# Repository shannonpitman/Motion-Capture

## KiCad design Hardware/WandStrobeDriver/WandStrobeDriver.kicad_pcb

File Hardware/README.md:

# Hardware — strobed wand for extrinsic calibration

KiCad 10 schematics for the pulsed marker wand that feeds `OpenMV/ExtrinsicsCalib`.
Two boards, schematic-only so far (no PCB layout yet).

| Directory | Build | Parts | Does |
|---|---|---|---|
| `WandStrobeDriver/` | ×1, at the handle | 20 | TLC555 astable + high-side P-FET; strobes all four markers together |
| `WandMarker/` | ×4, one per marker | 8 | 4× Kingbright L-7113SF7C in series + one ballast resistor |

```bash
python3 gen_schematics.py
```

`gen_schematics.py` writes both `.kicad_sch` files; change a value there and re-run
rather than editing the schematic by hand. `kisch.py` is a minimal schematic writer
and `kisym.py` pulls symbol geometry out of the stock KiCad libraries, so wire
endpoints come from real pin positions instead of being typed in.

## Rev B — what changed and why

Rev A ran **12 V** and put a **constant-current sink** on every marker board.
Both are gone.

The sink cost 1.6 V of headroom — a Vbe of sense, a Vce of regulation, and the
input Schottky — and that 1.6 V was the *entire* reason rev A needed 12 V. What it
bought was marker-to-marker matching of roughly 5 %. The bench data already shows
σ moving only ~3 % across a 20 % exposure range, and run-to-run repeatability of
the characterisation itself is ~3 %. So the sink was buying matching finer than the
measurement can resolve, at the price of a higher supply and eight extra parts per
marker board.

**The marker board is now the board that was already characterised, plus a
connector.** That is also why the existing boards plug straight into the driver.

Rev A is in git history if supply sensitivity ever turns out to matter.

## The rig

```
D
|
|                 D arm perpendicular at A, length >= |AC|/3
A-------------B---------C
<-----2/3-----><--1/3--->
```

A = origin, C = +X, D = +Y, as `ExtrinsicsCalib/README.md` defines them. Two wires
run from the driver to each marker: switched +9 V and a common ground. One timer
drives all four, so "dark" always means occluded, never out of phase.

## Why there is no diode across R2

This is the one place where the obvious simplification is the wrong one.

The standard trick for sub-50 % duty on a 555 is a diode across R2, and it assumes
the LEDs are on when **OUT is high**. They are not. `Q1` is P-channel on the
**high side** and conducts when **OUT is low** — so the short state is already the
state we want, and a plain astable with `R1 >> R2` gives 0.36 % duty with no diode
at all.

Adding the diode would force `R1` small, and `R1` then sinks `Vcc/R1` through the
DISCH pin for the whole 327 ms off-time — about **20 mA**, on a battery, against
the **9 µA** the circuit actually draws as built.

High-side switching also means every marker's return is permanently grounded, so a
chafed wire against the frame is a non-event rather than a short.

## Timing — three fixed parts

```
t_on   = 0.693 · R2 · C6              1075 µs
t_off  = 0.693 · (R1+R2) · C6          327 ms      ->  3.05 Hz
```

`R1 = 1 M`, `R2 = 3k3`, `C6 = 470 nF`. 1 MΩ is legal **only** because the TLC555 is
CMOS (pA input current); a bipolar NE555 would not hold this operating point.

3 Hz is `buildEasyWand`'s default `PulseHz`. Pulse grouping needs frame period <
pulse period with margin, and the 555 is a free-running RC oscillator — expect a few
percent of error and drift. That is fine, because alignment fits an offset and rate
per camera. Do not treat the strobe period as a known constant.

**`R2` sets pulse width, which is the brightness control.** Peak current is fixed by
the ballast resistor on each marker board, so the light delivered into one exposure
is `I × t_on`. Fit `R2` through-hole and clip a 5 k pot across its pads for bring-up,
then solder the nearest E24 value. The rate barely moves with it:

| R2 | t_on | | R2 | t_on |
|---|---|---|---|---|
| 1k8 | 586 µs | | **3k3** | **1075 µs** (fitted) |
| 2k2 | 717 µs | | 3k9 | 1270 µs |
| 2k7 | 879 µs | | 4k7 | 1531 µs |

**Every resistor on both boards is an E12 value** — 1M, 3k3, 220, 100k, 22k, 100,
and 68R on the markers. Nothing needs series pairs or an E24 stock.

The exact number does not matter. The 470 nF film capacitor is ±5 % on its own,
which is ±54 µs — larger than the gap between adjacent E12 steps at this end of
the range. `R2` is set empirically against a camera reading anyway, so treat
whatever you fit as a starting point.

## Supply — 9 V is sufficient

| Load | Average |
|---|---|
| TLC555 | ~1 mA |
| Timing network | 9 µA |
| D2 power indicator | ~0.35 mA |
| LEDs, 4 × 36 mA × 0.36 % | 0.52 mA |
| **Total** | **~1.9 mA** |

6×AA alkaline, or a PP3 for bench work. The timer, not the LEDs, dominates.

Headroom at 9 V, after the input Schottky (0.45 V) and bulk-cap droop (~0.2 V),
leaves 8.35 V across four LEDs and the ballast resistor. Comfortable — the string is
about 5.9 V, not the 6.4 V a flat 1.6 V per LED would suggest (see below).

`C1 = 1000 µF` covers the pulse: 4 × 36 mA × 1173 µs = 169 µC → 0.17 V droop.

## The emitter

**Kingbright L-7113SF7C**, 5 mm through-hole, GaAlAs, 850 nm (datasheet DSAB9772 V.16B).

| Parameter | Value | Conditions |
|---|---|---|
| Forward voltage | 1.4 typ / **1.6 max** | **at I_F = 20 mA** |
| DC forward current | **50 mA** | absolute max |
| Peak forward current | 1 A | 1/100 duty, **10 µs** pulse width |
| Power dissipation | 80 mW | absolute max |
| Radiant intensity | 30 typ mW/sr @ 20 mA, 90 @ 50 mA | |
| Viewing angle 2θ½ | **20°** | narrow — this is the ring artefact |

**1.6 V is not "the" forward drop.** It is the maximum *at 20 mA*. Vf climbs with
current and falls below 1.6 V under 20 mA. At 36 mA expect about 1.48 V each, so
four in series is ~5.9 V.

At 36 mA and 0.36 % duty each LED averages **0.19 mW against an 80 mW limit**.

## Setting the LED current

`R1` on each marker board. Same value on all four. Computed at 9 V less the driver's
Schottky and bulk-cap droop, using the real Vf curve rather than a flat 1.6 V:

| R1 | I_LED | Pulse for peak 210 at 4 m | Smear @ 0.3 m/s |
|---|---|---|---|
| 33R | 61 mA | 739 µs | 0.29 px |
| 47R | 48 mA | 951 µs | 0.37 px |
| **68R** | **36 mA** (fitted, matches the bench build) | **1263 µs** | **0.49 px** |
| 100R | 26 mA | 1729 µs | 0.67 px |

Measure across `TP1`–`TP2` with a scope during a pulse: `I = V(TP1) / R1`.

### The price of dropping the constant-current sink

0.3 V of battery sag moves the current **9 %**. The peak pixel value moves with it,
so re-target the exposure occasionally over a long session. It is a slow drift, not
noise, and the bench data shows σ changing only ~3 % across a 20 % exposure range —
so it costs well under 1 % of centroid accuracy. That is the whole trade, stated
plainly.

### Check the workbook number

`LED_characterisation.xlsx` lists **38.2 mA** for this build, computed by
`IR_LED_Parts_Calculator` from an assumed **Vf = 1.6 V** — which is the datasheet
*maximum at 20 mA*, not the value at 38 mA. With the real curve, 9 V through 68 Ω
gives about **43 mA**. Worth measuring once and correcting in the sheet, since that
column appears in the thesis.

## Bench test: build the driver first

Nothing in the driver cares about 9 V versus 12 V — the TLC555 runs 2–15 V and the
P-FET gate swings whatever the rail is. So build the driver, feed it a bench supply,
and hang the **existing** characterisation markers off J2–J5.

| Rail | Existing 68 Ω board draws |
|---|---|
| **9 V** | **36 mA** — the characterised operating point |
| 12 V | 74 mA |

At 9 V the strobe test is directly comparable with the DC rows in `A_Bench`. The
equivalence worth confirming is that the *peak pixel value* matches the DC bench row
once `R2` is set, because the camera in Regime B sees the peak, not the average.

Probe `TP1` (gate) against `TP3` (GND) on a scope before connecting any LED — that
confirms period and pulse width on their own.

## Breadboard variant — N-channel low side

The PCB uses a P-channel high-side switch. If the only MOSFETs to hand are
N-channel (IRF540N, IRF1010E), the bench build changes topology but nothing
optical or timing-related, so it still verifies what the breadboard is for.

**Move the switch to the low side.** All four marker grounds go to the FET
drain; source to GND; gate from the 555 through `R3`. An N-channel conducts
when the gate is **high**, so the flash must now be the OUT-**high** state —
the opposite of the PCB — which means the diode across R2 is now required.

| | PCB (P-ch high side) | Breadboard (N-ch low side) |
|---|---|---|
| `R1` charge path | 1 M | **3k3** |
| `R2` discharge | 3k3 | **1 M** |
| Diode across `R2` | none | **1N4148**, anode at DISCH, cathode at THR/TRIG |
| LEDs lit when OUT is | low | **high** |

Swap the two resistor values and add the diode. Timing comes out the same:
`t_on = 0.693 · 3k3 · 470n = 1075 µs`, `f = 3.06 Hz`, duty 0.33 %.

**What it costs.** During the 326 ms off-time the DISCH pin sinks `Vcc/R1` =
**2.7 mA** continuously, so the board goes from 1.9 mA to 4.6 mA average —
about 540 h on 6×AA instead of 1300. Fine for bench work, which is why the
PCB keeps the P-channel version.

(An earlier note in this file put that penalty at ~20 mA. That figure was for
rev A's 12 V rail and 300 µs pulse, where `R1` would have been ~920 Ω. At rev
B's 9 V and 1075 µs, `R1` is 3k3 and the penalty is 2.7 mA.)

**Headroom is unchanged** — 11 mV across an IRF540N at 144 mA against 10 mV
for the P-channel part. Both are irrelevant.

**What you lose:** with low-side switching the marker returns are no longer
permanently grounded, so the "a chafed wire against the frame is a non-event"
property goes away. Irrelevant on an isolated breadboard; it is one of the
reasons the PCB stays high-side.

Either FET works. Prefer the **IRF540N** — 71 nC of gate charge against the
IRF1010E's ~130 nC, and it only needs ~4 V of gate to pass 144 mA, so the
TLC555 drives it directly through `R3` with a few microseconds of edge against
a 1075 µs pulse. V_GS(th) is 2.0–4.0 V and V_GS max is ±20 V, so a 9 V swing
turns it hard on and stays well inside the gate rating.

**TO-220 tab is the DRAIN on both parts.** Low side, that puts the tab on the
marker-return node, not ground — keep it clear of anything earthed.

## Two parts you must not substitute casually

**Q1 (driver).** `DMP3098L-7` — **P-channel enhancement mode**, SOT-23
(Diodes Inc DS31447). The ratings that matter here:

| Parameter | Value | Why it matters |
|---|---|---|
| V_GSS | **±20 V** | the gate swings the whole rail, so this must exceed 9 V |
| V_GS(th) | −1.0 / −1.8 / −2.1 V | at −9 V the part is hard on, far past threshold |
| R_DS(on) | 70 mΩ max @ V_GS = −10 V | 10 mV across it at the 144 mA pulse |
| V_DSS | −30 V | 3× the rail |
| I_D | −3.8 A cont., −11 A pulsed | wildly over-specified at 144 mA, which is fine |
| Q_g | 7.8 nC @ −10 V | ~190 ns edge through R3, against a 1173 µs pulse |

**It must be enhancement mode, not depletion.** An enhancement device is OFF at
V_GS = 0, which is what R4 holds it at whenever the timer is not driving — so a
missing or unpowered TLC555 leaves the markers dark. A depletion device is ON at
V_GS = 0 and would sit the strings at DC with no strobe at all.

Any substitute needs V_GSS comfortably above 9 V. Do not fit a ±8 V part such as
Si2301; check the rating rather than assuming, since many SOT-23 P-FETs are ±12 V
and some are ±8 V.

**D1–D4 (marker).** Kingbright `L-7113SF7C`, footprint `LED_THT:LED_D5.0mm`. They are
marked **DNP** so a turnkey assembler skips them — they are hand-soldered so the
standoff to the diffuser can be set by hand. DNP excludes a part from the BOM and
position files, **not from the PCB**: the pads are still required.

## PCB layout - driver board

`gen_pcb.py` writes `WandStrobeDriver.kicad_pcb`. Nets are read from the
schematic netlist, so the board cannot silently disagree with the schematic
about connectivity; DRC is the check that the routing implements them.

```bash
kicad-cli sch export netlist --format kicadsexpr \
    -o WandStrobeDriver/WandStrobeDriver.net WandStrobeDriver/WandStrobeDriver.kicad_sch
python3 gen_pcb.py          # writes the board, then runs DRC
```

**80 x 60 mm, two layers, 1 oz.** 26 footprints, 95 track segments, 7 vias.
**DRC: 0 violations, 0 unconnected pads.**

The layout follows the rule from the design notes - switching current and the
high-impedance timing network occupy separate regions:

| Region | Holds |
|---|---|
| Top edge | J1, SW1, F1, D1 - the input chain, left to right |
| Upper middle | C1 bulk, C2, the indicator, R10/C3/C4 filtering VCC |
| Right | Q1 and the four marker connectors, so the pulse loop stays short |
| Lower left | U1 with R1, R2, C6, C5 - nothing switched crosses it |

**B.Cu is the ground return.** Only two signals use the back layer: the gate
escape from U1 pin 3 along `y = 83` (x 117.8 to 150) and its test-point stub at
`x = 142`. Every GND crossing of that line is placed outside that span, at
`x = 102.5` or `x = 155`, so the return is one connected tree. Through-hole
grounds reach it directly; the five SMD grounds each get a via.

There is also a B.Cu GND zone. It is **not filled in the file** - `kicad-cli`
cannot fill zones - but nothing depends on it: GND is routed with real tracks,
which is why DRC reports zero unconnected pads. Open the board in KiCad and
`Edit > Fill All Zones` to add the pour before making gerbers.

Fabrication outputs are in `WandStrobeDriver/fab/` (gerbers + Excellon drill),
and `WandStrobeDriver-PCB.pdf` is the top-side plot.

### If you move anything

Two clearances are deliberate and tight enough to check after any edit:

- The DISCH track at `y = 92.54` passes R2 pad 2 with 0.46 mm.
- The `+9V` feed to Q1 source at `x = 149` passes the gate via at (150, 83)
  with 0.4 mm.

## Still open

- **Marker board layout.** Not laid out yet. On the marker board the LED ring
  The LED ring must be exactly concentric with the centre datum (an asymmetric
  ring offsets the blob centroid by a fixed bias no filter can see), and the emitters aimed
  **tangentially** — the 20° viewing angle is what makes the marker ring, not the
  shell diameter. Do not fix the ring radius until Test G reports, because radius and
  wall thickness move the LED-to-wall standoff together.
- **Ambient IR.** Regime B needs a ~28 ms exposure and Test F (`F_Ambient`) has not
  been run. If the background floods it, the fallback is Regime A — short exposure,
  long pulse — which this board reaches by fitting a larger `R2`.
- **Which side D goes on.** The frame defines the *calibration* XY plane, not an
  electrical ground, so every marker keeps its own ground wire. easyWand takes
  origin, +X and +Y and lets **Z follow the right-hand rule**, so `A→C × A→D` must
  point **up**. Lay the rig flat, stand at A looking toward C, and D must be on your
  **left**. Put D on the right and Z points into the floor: every camera then solves
  below ground, mirrored, and it will not look like a sign error — it will look like
  a bad calibration.

## Verification

Both schematics pass with zero ERC violations, and the netlists have been checked
against the intended circuit:

```bash
kicad-cli sch erc --severity-all -o /tmp/erc.rpt WandStrobeDriver/WandStrobeDriver.kicad_sch
kicad-cli sch export netlist --format kicadsexpr -o /tmp/n.net WandMarker/WandMarker.kicad_sch
```

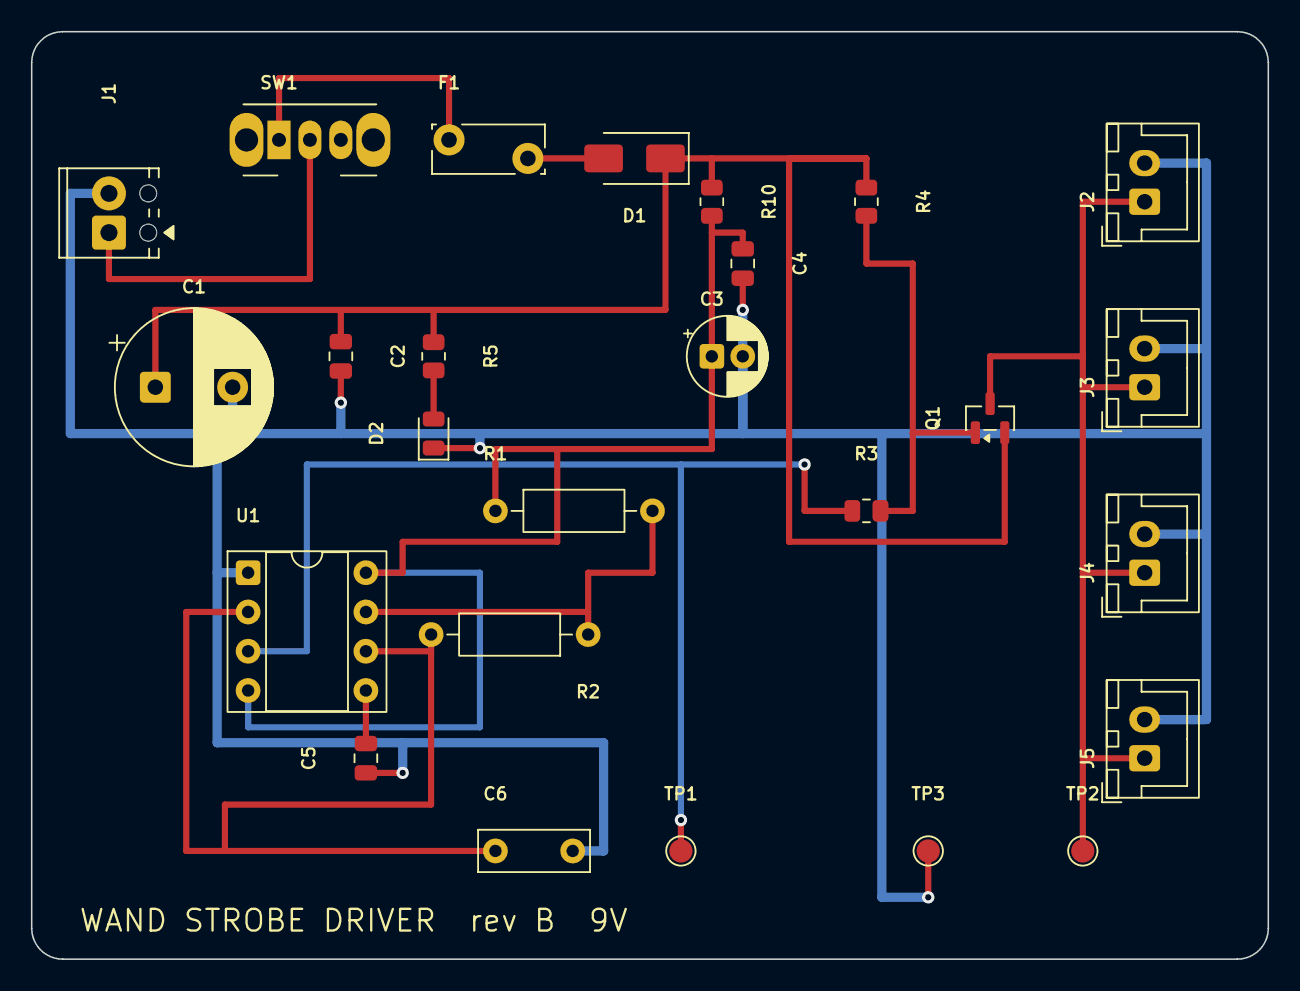
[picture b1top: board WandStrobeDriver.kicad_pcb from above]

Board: 2 copper layers, 80.0 x 60.0 mm, 26 parts (0 on the bottom side), 13 nets.

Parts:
C1: 1000u; CP_Radial_D10.0mm_P5.00mm
C2, C4: 100n; C_0805_2012Metric
C3: 10u; CP_Radial_D5.0mm_P2.00mm
C5: 10n; C_0805_2012Metric
C6: 470n; C_Rect_L7.0mm_W2.5mm_P5.00mm
D1: SS34; D_SMA
D2: PWR; LED_0805_2012Metric
F1: 500mA; Fuse_Bourns_MF-RG300
J1: 9V IN; TerminalBlock_Phoenix_MPT-0,5-2-2.54_1x02_P2.54mm_Horizontal
J2: MARKER A; JST_XH_B2B-XH-A_1x02_P2.50mm_Vertical
J3: MARKER B; JST_XH_B2B-XH-A_1x02_P2.50mm_Vertical
J4: MARKER C; JST_XH_B2B-XH-A_1x02_P2.50mm_Vertical
J5: MARKER D; JST_XH_B2B-XH-A_1x02_P2.50mm_Vertical
Q1: DMP3098L; SOT-23
R1: 1M; R_Axial_DIN0207_L6.3mm_D2.5mm_P10.16mm_Horizontal
R2: 3k3; R_Axial_DIN0207_L6.3mm_D2.5mm_P10.16mm_Horizontal
R3: 220; R_0805_2012Metric
R4: 100k; R_0805_2012Metric
R5: 22k; R_0805_2012Metric
R10: 100; R_0805_2012Metric
SW1: POWER; SW_Slide_SPDT_Angled_CK_OS102011MA1Q
TP1: GATE; TestPoint_Pad_D1.5mm
TP2: SW_LED; TestPoint_Pad_D1.5mm
TP3: GND; TestPoint_Pad_D1.5mm
U1: TLC555; DIP-8_W7.62mm_Socket

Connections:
+9V: C1.1, C2.1, D1.1, Q1.2, R4.1, R5.1, R10.1
/GATE: R3.1, TP1.1, U1.3
/SW_LED: J2.1, J3.1, J4.1, J5.1, Q1.3, TP2.1
GND: C1.2, C2.2, C3.2, C4.2, C5.1, C6.2, D2.1, J1.2, J2.2, J3.2, J4.2, J5.2, TP3.1, U1.1
unnamed: D1.2, F1.2
unnamed: D2.2, R5.2
unnamed: J1.1, SW1.2
unnamed: Q1.1, R3.2, R4.2
unnamed: F1.1, SW1.1
unnamed: C5.2, U1.5
unnamed: R1.2, R2.1, U1.7
unnamed: C6.1, R2.2, U1.2, U1.6
VCC: C3.1, C4.1, R1.1, R10.2, U1.4, U1.8

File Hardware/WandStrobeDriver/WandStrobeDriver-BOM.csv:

"Refs","Value","Footprint","Qty"
"C1","1000u/16V","Capacitor_THT:CP_Radial_D10.0mm_P5.00mm","1"
"C2,C4","100n","Capacitor_SMD:C_0805_2012Metric","2"
"C3","10u","Capacitor_THT:CP_Radial_D5.0mm_P2.00mm","1"
"C5","10n","Capacitor_SMD:C_0805_2012Metric","1"
"C6","470n film","Capacitor_THT:C_Rect_L7.0mm_W2.5mm_P5.00mm","1"
"D1","SS34","Diode_SMD:D_SMA","1"
"D2","PWR green","LED_SMD:LED_0805_2012Metric","1"
"F1","500mA","Fuse:Fuse_Bourns_MF-RG300","1"
"J1","9V IN","TerminalBlock_Phoenix:TerminalBlock_Phoenix_MPT-0,5-2-2.54_1x02_P2.54mm_Horizontal","1"
"J2","MARKER A (origin)","Connector_JST:JST_XH_B2B-XH-A_1x02_P2.50mm_Vertical","1"
"J3","MARKER B","Connector_JST:JST_XH_B2B-XH-A_1x02_P2.50mm_Vertical","1"
"J4","MARKER C (+X)","Connector_JST:JST_XH_B2B-XH-A_1x02_P2.50mm_Vertical","1"
"J5","MARKER D (+Y)","Connector_JST:JST_XH_B2B-XH-A_1x02_P2.50mm_Vertical","1"
"Q1","DMP3098L-7","Package_TO_SOT_SMD:SOT-23","1"
"R1","1M","Resistor_THT:R_Axial_DIN0207_L6.3mm_D2.5mm_P10.16mm_Horizontal","1"
"R2","3k3","Resistor_THT:R_Axial_DIN0207_L6.3mm_D2.5mm_P10.16mm_Horizontal","1"
"R3","220","Resistor_SMD:R_0805_2012Metric","1"
"R4","100k","Resistor_SMD:R_0805_2012Metric","1"
"R5","22k","Resistor_SMD:R_0805_2012Metric","1"
"R10","100","Resistor_SMD:R_0805_2012Metric","1"
"SW1","POWER","Button_Switch_THT:SW_Slide_SPDT_Angled_CK_OS102011MA1Q","1"
"TP1","GATE","TestPoint:TestPoint_Pad_D1.5mm","1"
"TP2","SW_LED","TestPoint:TestPoint_Pad_D1.5mm","1"
"TP3","GND","TestPoint:TestPoint_Pad_D1.5mm","1"
"U1","TLC555CP","Package_DIP:DIP-8_W7.62mm_Socket","1"

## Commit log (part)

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2026-02-18 Initial commit - colour tracking
2026-02-20 Reorganising repo with folders dedicated to different software/ languages, added MATLAB code
2026-02-20 Added UDP receiver comms
2026-02-20 Corrected EFK loop which runs regardless of whether a measurement update was received. Also corrected themeasurement function based on 3D indexing
2026-02-25 Adding USB connection
2026-02-26 Added timestamping + packaging of data over USB
2026-02-26 Added ROI windowing of blobs
2026-02-26 added ROI windowing and simultaneous colour tracking
2026-03-02 Debugged colour tracking code to properly parse data
2026-03-10 Lab colour thresholds updated
2026-03-10 Red colour thresholding bug
2026-03-10 fixed latency issue
2026-03-11 Correct latency calc in Matlab
2026-03-18 Wifi UDP capabilities of data transfer with MATLAB
2026-03-18 Added a log to compare the latency capabilities of wifi vs USB
2026-03-19 Addded logging to USB matlab script for loging differences in latency and frame to frame jitter comparison.
2026-03-19 Improved logging capabilities
2026-03-19 Comparison of latency and jitter
2026-04-16 depth tester code
